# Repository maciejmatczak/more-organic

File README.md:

# More organic

Last time (five-by-six) Freecad was used to achieve the parametric design of plate and rest of case parts.

Now, the whole design is more complicated. When keys were purely orthogonal, Freecad handled that easily with multi transform, but column stagger + thumb cluster is a bit more challenging.

OpenSCAD with SolidPython was choosen to support CAD design.

There is a couple of interdigitated parts in this project. Initially, the idea was to define everything in `make` dependencies, but that didn't work out. For example: case depends on switches placement (which are placed with script), but also manually placed elements on a PCB itself (uC, jack, etc). But PCB depends on a case itself, as PCB edge definition comes from it...

Whole workflow ended up as a subset of action from `Makefile`, saved intermediate design files within the repo itself (.scad, .dxf, .json data dumps).

This board might be really similar to quite a few already existing great boards out there. An additional knob would be also nice.

# Parts of this project

## Design

The design of shared data, like:

- keys and diode positions
- mounting holes (pcb to plate, plate standoffs)

... is generated from `design/design.py` file. A bit of a math, logic and magic numbers (hand measurments, etc).

## Case

With use of SolidPython and dump of the footrpints from PCB, the whole assembly of plate, cover and pcb design is generated:

Additionally, a collisions are shown in red (need of a manual validation):

The whole idea for this design is to be kind of _organic_. Edges are naturally created form particular elements being _melted_ with each other. I am proud of that one.

Some footprints from KiCAD were "redesigned" in OpenSCAD as well (basic shapes).

Different coordinate system between this 2 worlds (KiCAD and OpenSCAD) is not fun. Also, KiCAD and it's weird `(0, 0)` placement.

Also, this board doesn't have a bottom plate.

From python scripts .scad files are baked, then .dxf and images. .dxf are used as a PCBs edge lines (for main PCB, cover and plate).

## PCB

Ordinary PCB design. Needs manual routing followup after every `make pcb-place` is invoked, manual PCB edge reload from case's .dxf.

There is a small chaos in submodules and parts actually being used. The really used one, should be:

- [Keebio-Parts.pretty](github.com:keebio/Keebio-Parts.pretty)
- [keebio-components](github.com:keebio/keebio-components)
- [keyswitches.pretty](github.com/maciejmatczak/keyswitches.pretty), forked from [daprice's](github.com/daprice/keyswitches.pretty); I additionally modify one footprint to be reversible

# Afterthoughts

Scripting backup is great. But a really well thought and defined data flow needs be designed first to keep everything well working with each other in a more complicated design like this.

Clean stages of project are a key, I believe. Imagine if your work had to be done by different engineers. Mechanical design, electrical design. Which parts of a project are a common data that needs to be agreed and locked? And how to validate if you didn't mess up with some updates?

In a middle of a design, there would be a need to change something - for sure! The changes in the _root_ should naturally produce a dependant actions to follow up (that's should be clearly visible). Steps should be clear.

Status quo is not exactly how I was imaging it, but with recent RSI issues being more severe, this project took longer than I thought. And one failed fabrication ;).

Highlights:

- KiCAD design scripting
  - data dumpers from a KiCAD PCB
  - footprint placers from such dump - with filtering included
- OpenSCAD and SolidPython
  - idea for a companion libraries (to KiCAD's)
- General project validation - pytest suite
  - checking characteristic elements in designs (number of holes)
  - proper file age (drc report should be **younger** than a design itself)

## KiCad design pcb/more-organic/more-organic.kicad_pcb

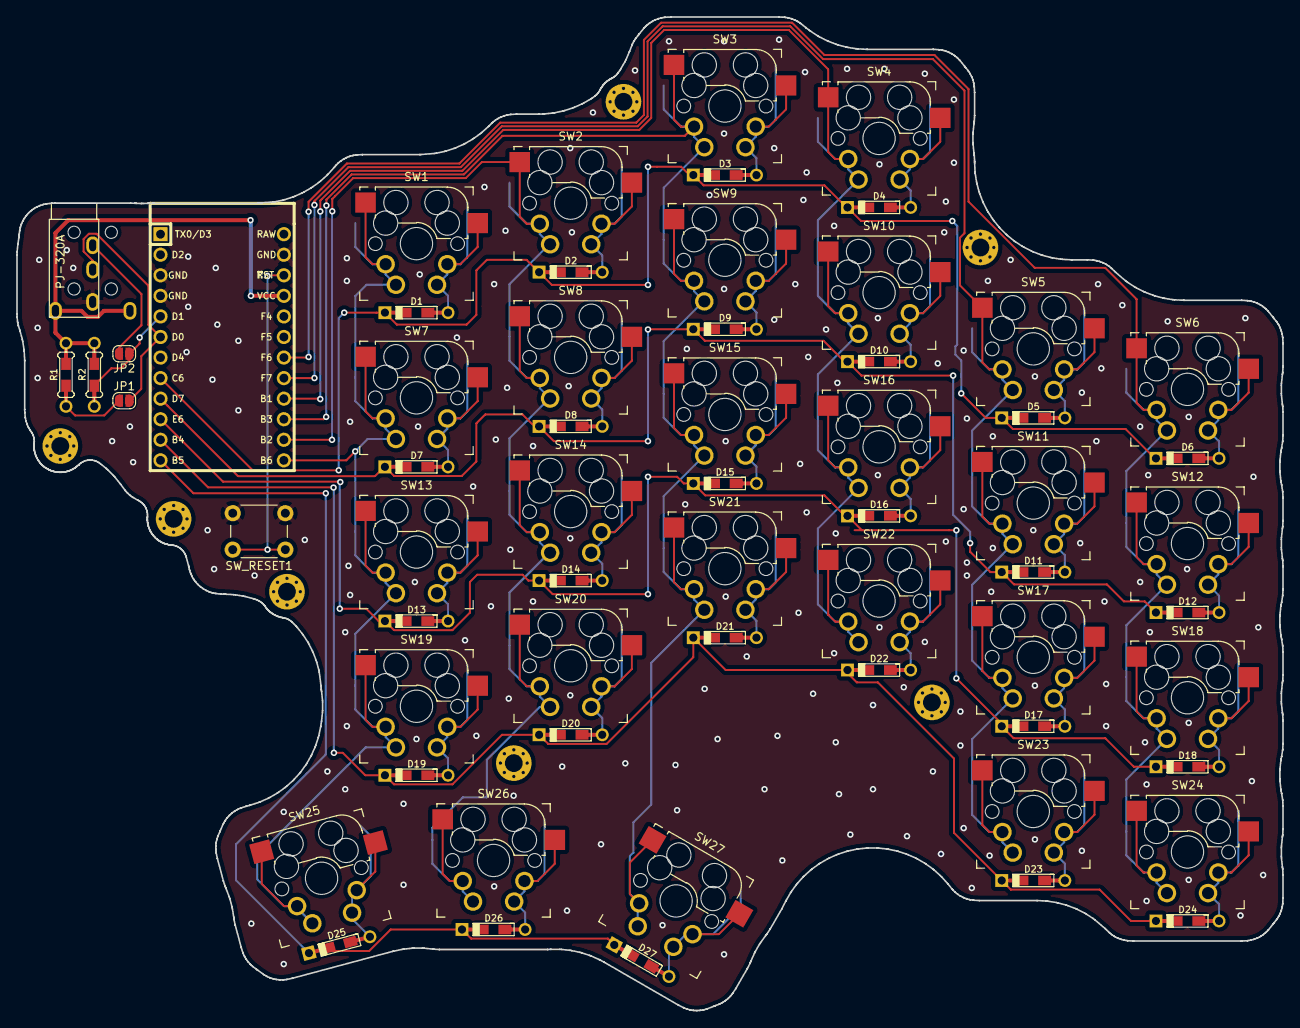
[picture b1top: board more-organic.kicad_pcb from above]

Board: 2 copper layers, 156.4 x 122.7 mm, 65 parts (0 on the bottom side), 45 nets.

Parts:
D1, D2, D3, D4, D5, D6, D7, D8, D9, D10, D11, D12, D13, D14, D15, D16, D17, D18, D19, D20, D21, D22, D23, D24, D25, D26, D27: D; Diode-dual
JP1, JP2: SolderJumper_2_Open; SolderJumper-2_P1.3mm_Open_RoundedPad1.0x1.5mm
R1, R2: R; Resistor-Hybrid
SW1, SW2, SW3, SW4, SW5, SW6, SW7, SW8, SW9, SW10, SW11, SW12, SW13, SW14, SW15, SW16, SW17, SW18, SW19, SW20, SW21, SW22, SW23, SW24, SW25, SW26, SW27: SW_Push; Kailh_socket_MX_optional_reversible_alt
SW_RESET1: MX; SW_PUSH_6mm_H7.3mm
U1: ProMicro; ArduinoProMicro
U2: TRRS; TRRS-PJ-320A-dual
generated: MountingHole_2.2mm_M2_Pad_Via
generated#2, generated#3, generated#4: MountingHole_2.2mm_M2_Pad_Via

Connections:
/col0: SW1.1, SW7.1, SW13.1, SW19.1, SW25.1, U1.13
/col1: SW2.1, SW8.1, SW14.1, SW20.1, SW26.1, U1.14
/col2: SW3.1, SW9.1, SW15.1, SW21.1, SW27.1, U1.15
/col3: SW4.1, SW10.1, SW16.1, SW22.1, U1.16
/col4: SW5.1, SW11.1, SW17.1, SW23.1, U1.17
/col5: SW6.1, SW12.1, SW18.1, SW24.1, U1.18
/row0: D1.1, D2.1, D3.1, D4.1, D5.1, D6.1, U1.8
/row1: D7.1, D8.1, D9.1, D10.1, D11.1, D12.1, U1.9
/row2: D13.1, D14.1, D15.1, D16.1, D17.1, D18.1, U1.10
/row3: D19.1, D20.1, D21.1, D22.1, D23.1, D24.1, U1.11
/row4: D25.1, D26.1, D27.1, U1.12
/rst: SW_RESET1.1, U1.22
/scl_uart: JP1.2, U1.6, U2.3
/sda: JP2.1, R2.1, U1.5
/xtradata: JP2.2, U2.4
GND: SW_RESET1.2, U1.3, U1.4, U1.23, U2.2
unnamed: D1.2, SW1.2
unnamed: D2.2, SW2.2
unnamed: D3.2, SW3.2
unnamed: D4.2, SW4.2
unnamed: D5.2, SW5.2
unnamed: D6.2, SW6.2
unnamed: D7.2, SW7.2
unnamed: D8.2, SW8.2
unnamed: D9.2, SW9.2
unnamed: D10.2, SW10.2
unnamed: D11.2, SW11.2
unnamed: D12.2, SW12.2
unnamed: D13.2, SW13.2
unnamed: D14.2, SW14.2
unnamed: D15.2, SW15.2
unnamed: D16.2, SW16.2
unnamed: D17.2, SW17.2
unnamed: D18.2, SW18.2
unnamed: D19.2, SW19.2
unnamed: D20.2, SW20.2
unnamed: D21.2, SW21.2
unnamed: D22.2, SW22.2
unnamed: D23.2, SW23.2
unnamed: D24.2, SW24.2
unnamed: D25.2, SW25.2
unnamed: D26.2, SW26.2
unnamed: D27.2, SW27.2
unnamed: JP1.1, R1.1
VCC: R1.2, R2.2, U1.21, U2.1

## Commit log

2020-08-02 Create LICENSE
2020-08-02 Inital add submodules, scripts, tasks.py
2020-08-02 Add Cole Markham's parts library
2020-08-02 Add fork of daprice's keyswitches
2020-08-02 Add initial board, start working on PCB placer script
2020-08-02 Add gitignore
2020-08-02 Switch to fork's feature branch
2020-08-22 Add build folder
2020-08-22 Add makefile
2020-08-22 Add requirements.txt
2020-08-22 Add Python stuff to gitignore
2020-08-22 Rework on design process, case files
2020-08-22 Add readme, images
2020-08-22 Add dxf output, lost the 3D view from the same design
2020-08-23 Rewrite makefile to use special variables
2020-08-23 Modify export to support different projection and png in one
2020-09-03 Specify scad file for watch task
2020-09-03 Add screw holes
2020-09-03 Fix bug on swtich cutout positioning
2020-09-03 Add screw and screw holes
2020-09-03 Hierarchicalize the parts of design
    Sub elements are totally seperated now, assembly is a different view as well.
2020-09-07 Add python-dotenv
2020-09-07 Add phony case target
2020-09-07 Add initial cover design
2020-09-07 Add reserved space and 3d model of arduino
2020-09-07 Fix rotating math (KiCAD y axis...)
2020-09-07 Update pcb with recent placement, remove 3 not used switches
2020-09-07 Move, update pcb scripts
2020-09-07 Remove unneccessary file
2020-09-07 Add pcb targets (placer)
2020-09-13 Redesigning makefile, design and pcb data flow
2020-09-13 Add dumper for PCB data
2020-09-13 Follow up with new data flow on case
2020-09-13 Add rest of the designs
2020-09-13 Follow up with make rules
2020-09-19 Make scripts civil - using argparse
2020-09-19 Rename small case to cover
2020-09-19 Add load dotenv
2020-09-19 Add non existing option for footprint dump
2020-09-19 clean up
2020-09-19 Remove not needed section
2020-09-19 Routed current pcb
2020-09-19 Add "generated" reference fencing to do not delete too much
2020-09-19 Add lock
2020-09-19 Add cover and plate makefile placer commands
2020-09-19 Add simple filtering args
2020-09-19 Move main pcb files
2020-09-19 Add plotting
2020-09-19 Remove all target
2020-09-19 Add cove design
2020-10-25 Move design data output to data folder
2020-10-25 Follow up with missing files (data/design)
2020-10-25 Move case output files to data/case
2020-10-25 Move footprint dump to data/pcb
2020-10-25 Redesign thumb cluster
2020-10-25 Add missing mh from pcb to plate
2020-10-25 Swtich plate place command to use pcb dump
2020-10-31 Adjust key placement
2020-10-31 Regenerate dxfs
2020-10-31 Update pcb
2020-10-31 Add x_gt functionality
2020-10-31 Fix plate-place
2020-10-31 Replace the mounting holes
2020-10-31 Regenerate
2020-10-31 Add tests for pcb validation
2020-10-31 Move fab files to FAB folder
2020-10-31 Add FAB folder
2020-11-01 Add fab files age validation
2020-11-01 Small tweaks, regenerate PCB
2020-11-01 Readme updates
2020-11-01 Update case image
2020-11-01 Rerun drc
2021-02-06 Readme...
2021-02-06 Remove unused M2 pcb to cover from design.py
2021-02-09 Change the column offsets post 1 fab
    After 1 fab keyboard seemed to be too aggressive. Boo hoo.
    Lessons learned. New measurments. And halfing it either way.
2021-02-09 Modify test to expect 6 holes in PCB
2021-02-09 Newest pcb report
2021-02-09 Route new switch placement
2021-02-13 Regenerate plate
2021-02-13 Modify test: plate to have 7 mounting holes
